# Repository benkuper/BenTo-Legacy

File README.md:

# BenTo
Legacy repository for the Bento Clubs

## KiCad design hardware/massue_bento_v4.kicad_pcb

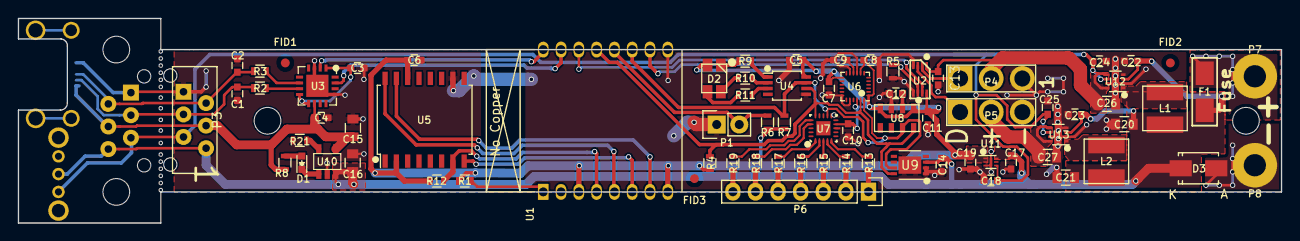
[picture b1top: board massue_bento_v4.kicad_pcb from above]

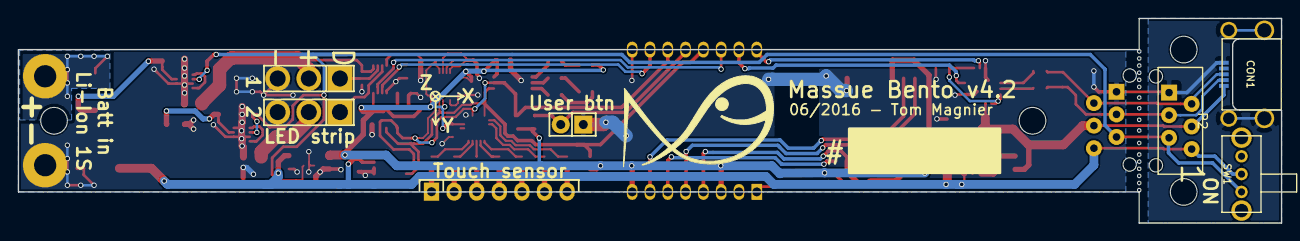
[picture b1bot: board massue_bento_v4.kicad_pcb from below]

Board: 2 copper layers, 142.0 x 23.0 mm, 79 parts (3 on the bottom side), 54 nets.

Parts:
C1, C2: 47pF; C_0603
C3, C4, C5, C6, C7, C9, C10, C11, C12, C13, C18, C24, C25: 0.1uF; C_0603
C8: 10nF; C_0603
C14, C17, C19: 2.2uF; C_0603
C15, C16: 10uF; C_0805
C20, C21: 4.7uF, 10V, X5R/X7R; C_0805
C22, C23: 2.2uF, 10V, X5R/X7R; C_0603
C26, C27: 22uF, 10V, ESR < 10mR, X5R/X7R; C_0805
CON1: USB-MICRO-B; MICRO_USB_B_MIDMOUNT_TH
D1: Red; LED-0603
D2: Cree CLV1A; PLCC-4
D3: PMEG4050EP; SMA_Standard
F1: SMD FUSE, 8A; Fuse_SMD1206_HandSoldering
FID1, FID2, FID3: Fiducial_very_small_modern
L1, L2: 1uH, 4.5A (LQH5BPN1R0NT0L); LQH5BP_Murata_ind
P1: CONN_01X02; Socket_Strip_Straight_1x02
P2, P3: CONN_01X06; MOLEX_90325-0006
P4, P5: CONN_01X03; Conn_1x03_1-8mmDrill
P6: CONN_01X07; Socket_Strip_Straight_1x07
P7, P8: CONN_01X01; SolderWirePad_single_2-5mmDrill
R1, R4, R5, R6, R7, R13, R14, R15, R16, R17, R18, R19: 10k; R_0603
R2, R3: 27R; R_0603
R8: 1k; R_0603
R9: 220R; R_0603
R10, R11: 100R; R_0603
R12: 100k; R_0603
R21: 2k; R_0603
SW1: SWITCH_INV; SPDT_MINI_SLIDE_SWITCH
U1: ESP-07v2
U2: SN74LVC2T45DCU; VSSOP-8
U3: FT230XQ; QFN-16-1EP_4x4mm_Pitch0.65mm
U4: PCA9632; TSSOP-8_3x3mm_Pitch0.65mm
U5: S25FL***; SOIC-16_7.5x10.3mm_Pitch1.27mm
U6: MPU9250; QFN-24-3x3mm_Pitch0.4mm
U7: AT42QT1070-MMH; QFP_20_3x3mm_0.45mm_pitch
U8: MPL3115A2; LGA8
U9: LC709203F; WDFN-8-1EP_3x4mm_Pitch0.65mm
U10: MCP73832; SOT-23-5
U11: MIC5528-3.3YMT; DFN-6-1EP_1.2x1.2mm_Pitch0.4mm
U12, U13: MIC2876-5.0YMT; DFN-8-1EP_2x2mm_Pitch0.5mm

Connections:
+3V3: C5.1, C6.1, C7.1, C8.1, C10.1, C11.1, C19.1, D2.2, R1.1, R4.1, R6.1, R7.1, R12.1, U1.3, U1.8, U2.8, U4.8, U5.2, U5.14, U6.1, U6.8, U6.13, U6.22, U7.9, U8.1, U8.4, U11.1, U11.2
+5V_1: C13.1, C26.1, P4.2, U2.1, U12.5, U12.8
+5V_2: C27.1, P5.2, U13.5, U13.8
+5V_USB: C4.2, C15.1, CON1.1, P2.4, P3.4, R8.2, U3.10, U10.4
+BATT: C14.1, C16.1, C17.1, C20.1, C21.1, C22.1, C23.1, D3.1, F1.2, L1.1, L2.1, P2.6, P3.6, SW1.2, U9.3, U10.3, U11.6, U12.3, U13.3
/+3.3V_FTDI: C3.1, U3.1, U3.8, U3.9
/BTN/BOOTL: P1.2, R6.2, U1.12
/FLASH_CS: R12.2, U1.4, U5.7
/FTDI_RX: U1.16, U3.2
/FTDI_TX: U1.15, U3.15
/LED1_3.3V: U1.14, U2.7
/LED1_5V: P4.1, U2.2
/LED2_3.3V: R5.1, U1.10, U2.6
/LED2_5V: P5.1, U2.3
/MISO: U1.6, U5.8
/MOSI: U1.7, U5.15
/Power/CHRG_STAT: D1.1, U10.1
/Power/ENABLE: C18.1, C24.1, C25.1, P2.5, P3.5, SW1.1, U11.4, U12.6, U13.6
/SCK: U1.5, U5.16
/Sensors/SCL: R4.2, U1.13, U4.6, U6.23, U7.15, U8.8, U9.8
/Sensors/SDA: R7.2, U1.11, U4.7, U6.24, U7.12, U8.7, U9.7
GND: C1.2, C2.2, C3.2, C4.1, C5.2, C6.2, C7.2, C8.2, C9.2, C10.2, C11.2, C12.2, C13.2, C14.2, C15.2, C16.2, C17.2, C18.2, C19.2, C20.2, C21.2, C22.2, C23.2, C24.2, C25.2, C26.2, C27.2, CON1.5, CON1.6, CON1.7, CON1.8, CON1.9, D3.2, P1.1, P2.1, P3.1, P4.3, P5.3, P8.1, R5.2, R21.2, U1.9, U2.4, U2.5, U3.3, U3.13, U3.17, U4.5, U5.10, U6.9, U6.11, U6.18, U6.20, U7.8, U7.11, U8.3, U9.1, U9.2, U9.9, U10.2, U11.3, U11.7, U12.2, U12.4, U12.7, U12.9, U13.2, U13.4, U13.7, U13.9
unnamed: C1.1, CON1.2, P2.3, P3.3, R2.2
unnamed: C2.1, CON1.3, P2.2, P3.2, R3.2
unnamed: C9.1, U6.10
unnamed: C12.1, U8.2
unnamed: D1.2, R8.1
unnamed: D2.1, R9.1
unnamed: D2.3, R11.1
unnamed: D2.4, R10.1
unnamed: F1.1, P7.1
unnamed: L1.2, U12.1
unnamed: L2.2, U13.1
unnamed: P6.1, R13.1
unnamed: P6.2, R14.1
unnamed: P6.3, R15.1
unnamed: P6.4, R16.1
unnamed: P6.5, R17.1
unnamed: P6.6, R18.1
unnamed: P6.7, R19.1
unnamed: R1.2, U1.1
unnamed: R2.1, U3.7
unnamed: R3.1, U3.6
unnamed: R9.2, U4.1
unnamed: R10.2, U4.2
unnamed: R11.2, U4.3
unnamed: R13.2, U7.5
unnamed: R14.2, U7.4
unnamed: R15.2, U7.3
unnamed: R16.2, U7.2
unnamed: R17.2, U7.1
unnamed: R18.2, U7.17
unnamed: R19.2, U7.16
unnamed: R21.1, U10.5

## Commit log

2017-04-20 BentoV4 update
